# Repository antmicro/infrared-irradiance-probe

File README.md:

# Infrared Irradiance Probe

Copyright (c) 2022-2023 [Antmicro](https://www.antmicro.com)

## Overview

This project contains open hardware design files for a simple detector of infrared (IR) radiation.
It features two photodiodes with peak sensitivity of 900nm and 940nm, and signal-forming circuitry with adjustable gain.
The board can be used for measuring relative intensity of IR radiation and for probing dynamic illumination parameters of infrared LEDs and laser modules.

The design files were prepared in KiCad 6.x.

## Project structure 

The main directory contains KiCad PCB design files, a LICENSE and a README.
The remaining files are stored in the following directories: 

* `lib` - contains the component libraries, 
* `img` - contains graphics for this README,
* `assets` - contains visual assets used for showcasing this board on [Open Hardware Portal](https://openhardware.antmicro.com)

## Key features

* Two photodiodes for measuring IR irradiance (peak sensitivity @ 900nm for diode on top and 940nm for the bottom one)
* BNC connector for oscilloscope measurements
* Regulated sensitivity
* I2C single-channel interface for digital signal probing
* Selectable power source (USB-C / JST / external power supply)

## License

This project is licensed under the [Apache-2.0](LICENSE) license.

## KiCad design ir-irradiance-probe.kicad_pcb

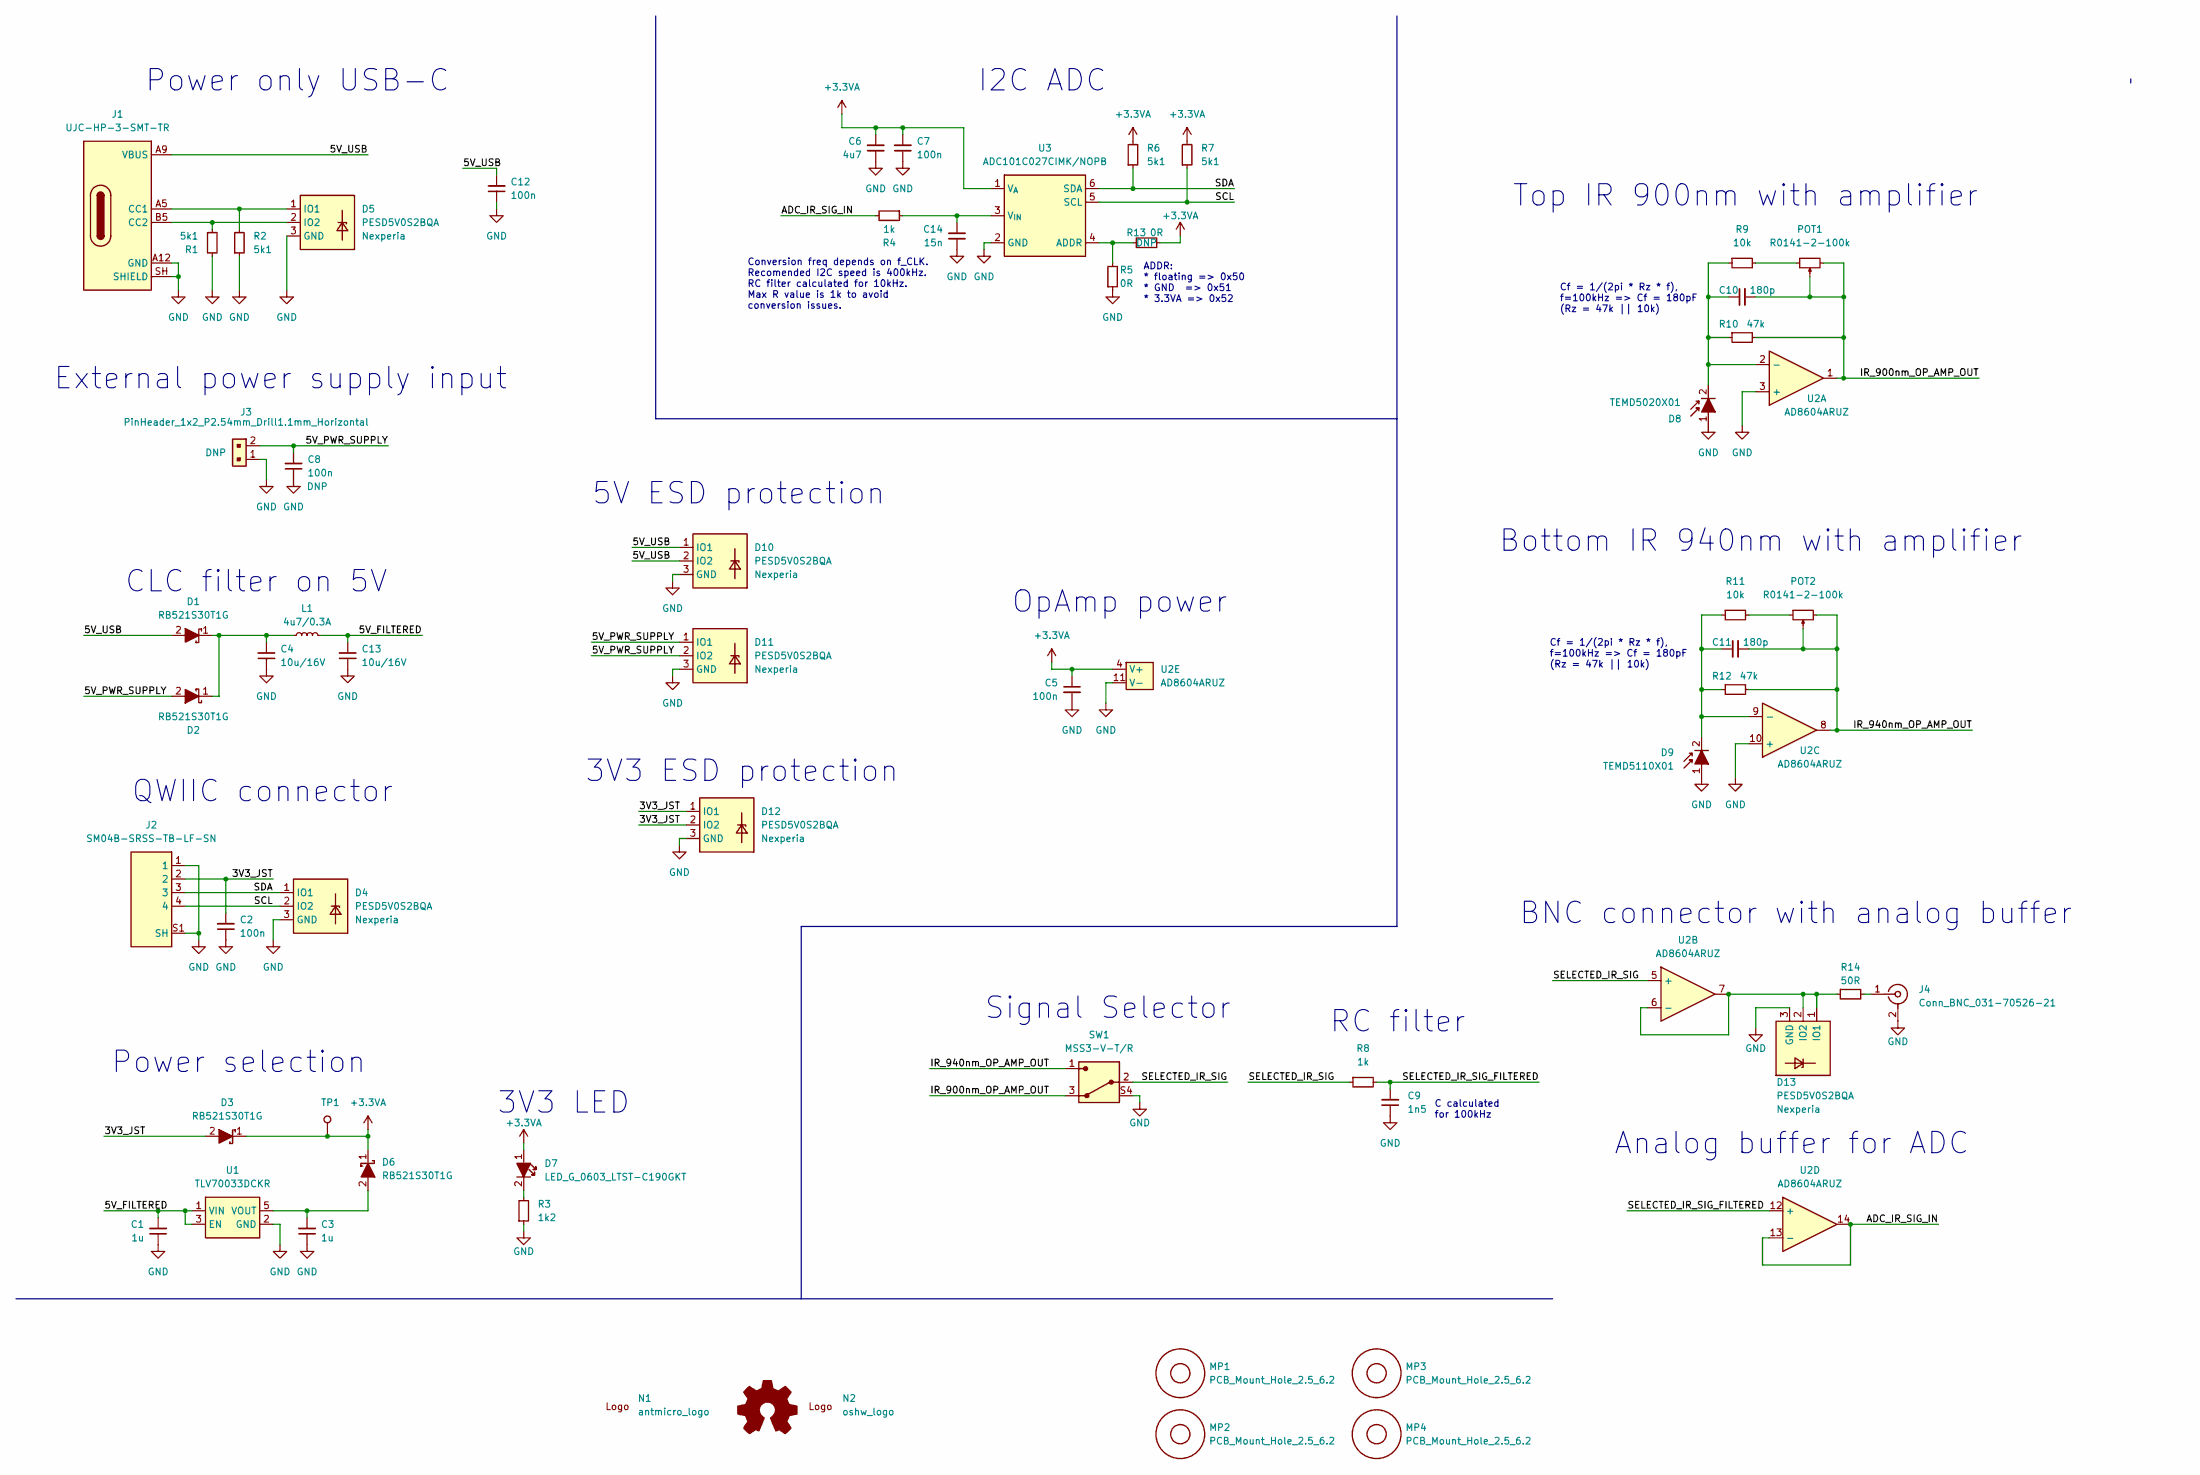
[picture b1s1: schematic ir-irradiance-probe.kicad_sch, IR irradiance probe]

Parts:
C1, C3: C_1u_0402; C_0402_1005Metric; MPN C1005X6S1A105K050BC
C2, C5, C7, C8, C12: C_100n_0402; C_0402_1005Metric; Voltage 50V; MPN GRM155R61H104KE14D
C4, C13: C_10u_16V_0603; C_0603_1608Metric; MPN GRM188C81C106MA73D
C6: C_4u7_0603; C_0603_1608Metric; MPN C1608X5R1V475M080AC
C9: C_1n5_0402; C_0402_1005Metric; MPN 885012205007
C10, C11: C_180p_0402; C_0402_1005Metric; MPN 04025A181JAT2A
C14: C_15n_0402; C_0402_1005Metric; MPN GRM155R71C153KA01D
D1, D2, D3, D6: RB521S30T1G; SOD-523; MPN RB521S30T1G
D4, D5, D10, D11, D12, D13: PESD5V0S2BQA; TPD2E009DRTR; MPN PESD5V0S2BQA
D7: LED_G_0603_LTST-C190GKT; LED_0603_1608Metric_G; MPN LTST-C190GKT
D8: TEMD5020X01; Photodiode_SMD_4.2x5mm_TEMD; MPN TEMD5020X01
D9: TEMD5110X01; Photodiode_SMD_4.2x5mm_TEMD; MPN TEMD5110X01
J1: USB-C_UJC-HP-3-SMT-TR; MPN UJC-HP-3-SMT-TR
J2: SM04B-SRSS-TB-LF-SN; MPN SM04B-SRSS-TB(LF)(SN)
J3: PinHeader_1x2_P2.54mm_Drill1.1mm_Horizontal; PinHeader_1x02_P2.54mm_Horizontal; MPN 61300211021
J4: Conn_BNC_031-70526-21; MPN 031-70526-21
L1: L_4u7_0.3A_0805; L_0805_2012Metric; MPN MLZ2012M4R7HT000
MP1, MP2, MP3, MP4: PCB_Mount_Hole_2.5_6.2; mounting-hole-2.75mm-M2.5_D6.2mm_PTH
N1: antmicro_logo; antmicro-logo_scaled_20mm
N2: oshw_logo; oshw-logo
POT1, POT2: POT_100k_R0141-2-100k; POT_R0141-2; MPN R0141-2-100k
R1, R2, R6, R7: R_5k1_0402; R_0402_1005Metric; Tolerance 1%; MPN CR0402-FX-5101GLF
R3: R_1k2_0402; R_0402_1005Metric; Tolerance 1%; MPN CR0402-FX-1201GLF
R4, R8: R_1k_0402; R_0402_1005Metric; Tolerance 1%; MPN CR0402-FX-1001GLF
R5, R13: R_0R_0402; R_0402_1005Metric; MPN ERJ2GE0R00X
R9, R11: R_10k_0402; R_0402_1005Metric; Tolerance 1%; MPN CR0402-FX-1002GLF
R10, R12: R_47k_0402; R_0402_1005Metric; Tolerance 1%; MPN CR0402-FX-4702GLF
R14: R_50R_0402; R_0402_1005Metric; Tolerance 1%; MPN CR0402-FX-50R0GLF
SW1: MSS3-V-T_R; Switch_Slide_MSS3; MPN MSS3-V-T/R
TP1: TP_0.75mm_SMD; TP_SMD_0.75mm
U1: TLV70033_SC70; SC-70-5; MPN TLV70033DCKR
U2: AD8604ARUZ; TSSOP-14_4.4x5mm_P0.65mm; MPN AD8604ARUZ
U3: ADC101C027CIMK; SOT-23-6; MPN ADC101C027CIMK/NOPB

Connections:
+3.3VA: C5.1, C6.2, C7.2, D3.1, D6.1, D7.1, R6.2, R7.2, R13.1, TP1.1, U2.4 (V+), U3.1 (V_{A})
/3V3_JST: C2.2, D3.2, D12.1 (IO1), D12.2 (IO2), J2.2
/5V_FILTERED: C1.2, C13.2, L1.2, U1.1 (VIN), U1.3 (EN)
/5V_PWR_SUPPLY: C8.2, D2.2, D11.1 (IO1), D11.2 (IO2), J3.2
/5V_USB: C12.2, D1.2, D10.1 (IO1), D10.2 (IO2), J1.A9 (VBUS), J1.B9 (VBUS)
/ADC_IR_SIG_IN: R4.2, U2.13 (-), U2.14
/IR_900nm_OP_AMP_OUT: C10.2, POT1.2, POT1.3, R10.2, SW1.3, U2.1
/IR_940nm_OP_AMP_OUT: C11.2, POT2.2, POT2.3, R12.2, SW1.1, U2.8
/SCL: D4.2 (IO2), J2.4, R7.1, U3.5 (SCL)
/SDA: D4.1 (IO1), J2.3, R6.1, U3.6 (SDA)
/SELECTED_IR_SIG: R8.1, SW1.2, U2.5 (+)
/SELECTED_IR_SIG_FILTERED: C9.2, R8.2, U2.12 (+)
GND: C1.1, C2.1, C3.1, C4.1, C5.2, C6.1, C7.1, C8.1, C9.1, C12.1, C13.1, C14.1, D4.3 (GND), D5.3 (GND), D8.1, D9.1, D10.3 (GND), D11.3 (GND), D12.3 (GND), D13.3 (GND), J1.A12 (GND), J1.B12 (GND), J1.SH (SHIELD), J2.1, J2.S1 (SH), J2.S2 (SH), J3.1, J4.2, R1.2, R2.1, R3.1, R5.1, SW1.S1 (SH), SW1.S2 (SH), SW1.S3 (SH), SW1.S4 (SH), U1.2 (GND), U2.3 (+), U2.10 (+), U2.11 (V-), U3.2 (GND)
unnamed: C3.2, D6.2, U1.5 (VOUT)
unnamed: C4.2, D1.1, D2.1, L1.1
unnamed: C10.1, D8.2, R9.1, R10.1, U2.2 (-)
unnamed: C11.1, D9.2, R11.1, R12.1, U2.9 (-)
unnamed: C14.2, R4.1, U3.3 (V_{IN})
unnamed: D5.1 (IO1), J1.A5 (CC1), R2.2
unnamed: D5.2 (IO2), J1.B5 (CC2), R1.1
unnamed: D7.2, R3.2
unnamed: D13.1 (IO1), D13.2 (IO2), R14.1, U2.6 (-), U2.7
unnamed: J4.1, R14.2
unnamed: POT1.1, R9.2
unnamed: POT2.1, R11.2
unnamed: R5.2, R13.2, U3.4 (ADDR)

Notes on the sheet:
Signal Selector
CLC filter on 5V
BNC connector with analog buffer
Top IR 900nm with amplifier
ADDR: * floating => 0x50 * GND => 0x51 * 3.3VA => 0x52
RC filter
3V3 ESD protection
Cf = 1/(2pi * Rz * f), f=100kHz => Cf = 180pF (Rz = 47k || 10k)
I2C ADC
Conversion freq depends on f_CLK. Recomended I2C speed is 400kHz. RC filter calculated for 10kHz. Max R value is 1k to avoid conversion issues.
Power only USB-C
Analog buffer for ADC
Power selection
External power supply input
OpAmp power
QWIIC connector
Bottom IR 940nm with amplifier
3V3 LED
5V ESD protection
C calculated for 100kHz

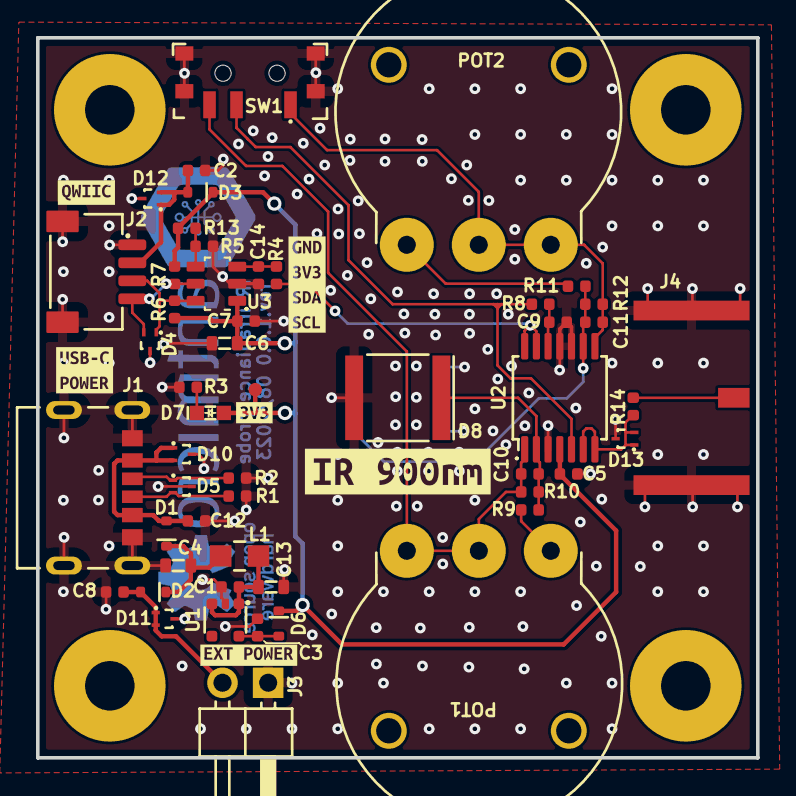
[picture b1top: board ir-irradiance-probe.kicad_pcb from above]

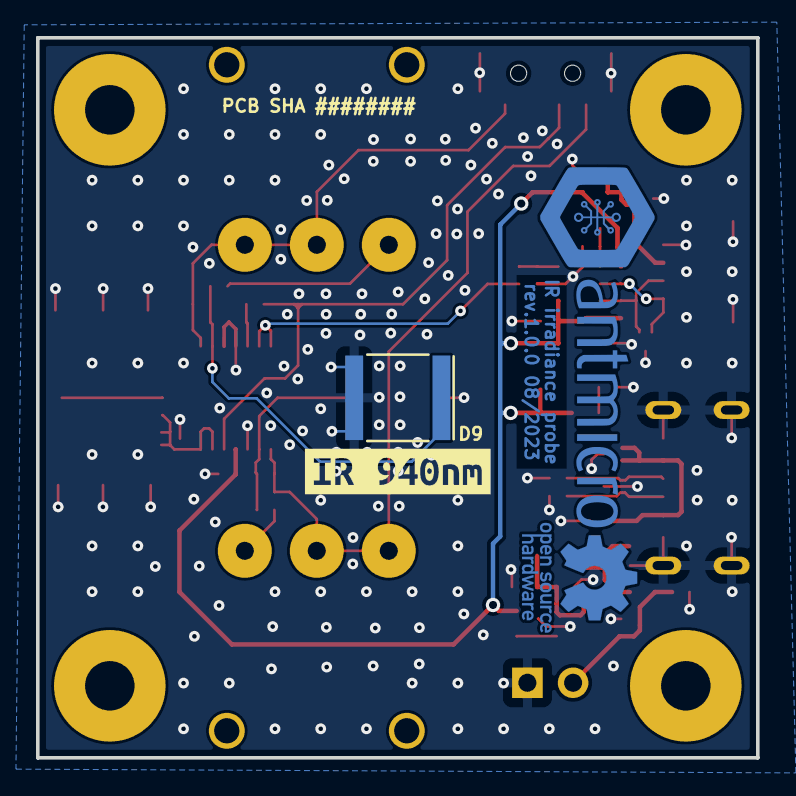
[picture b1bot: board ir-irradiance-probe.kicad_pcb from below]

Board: 2 copper layers, 40.0 x 40.0 mm, 66 parts (4 on the bottom side), 26 nets.

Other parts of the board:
kibuzzard-64C24E37: G***; kibuzzard-64C24E37
kibuzzard-64C24E46: G***; kibuzzard-64C24E46
kibuzzard-64DA12EE: G***; kibuzzard-64DA12EE
kibuzzard-64DA14BC: G***; kibuzzard-64DA14BC
kibuzzard-64DA143B: G***; kibuzzard-64DA143B
kibuzzard-64DA1325: G***; kibuzzard-64DA1325
kibuzzard-64E321C3: G***; kibuzzard-64E321C3

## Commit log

2023-07-27 [#47284] Create empty kicad project
2023-07-27 [#47284] Add README file
2023-07-27 [#47284] Add layout for visual reference and power connectors on sch
2023-07-27 [#47284] Add ADC and mounting holes on sch
2023-07-28 [#47284] Update block diagram
2023-07-28 [#47284] Add analog section to sch
2023-07-28 [#47284] Add power section
2023-08-03 [#47284] Update RC filter with C value
2023-08-03 [#47284] Connect IR signals to the switch
2023-08-03 [#47284] Complete circuit for I2C ADC
2023-08-03 [#47284] Add TVS diodes on USB-C and QWIIC connectors
2023-08-03 [#47284] Add 100n capacitor on OpAmp power pin
2023-08-03 [#47284] Add proper values for CLC filter
2023-08-03 [#47284] Update C values in OpAmp circuit and annotate schematic
2023-08-03 [#47284] Update schematic with symbols from antmicro symlib
2023-08-03 [#47284] Add LED indicator on 3V3 power line
2023-08-07 [#47284] Update potentiometers for amplifiers
2023-08-07 [#47284] Cleaned schematic
2023-08-07 [#47284] Migrated project back to KiCad v6
2023-08-07 [#47284] Minor fixes in schematic
2023-08-07 [#47284] Prepare preliminary components layout
2023-08-09 [#47284] Update potentiometer after standardisation
2023-08-09 [#47284] Create local components library
2023-08-09 [#47284] Change potentiometers on schematic
2023-08-09 [#47284] Rework PCB layout to fit 4x4cm board
2023-08-09 [#47284] Change pin header to horizontal
2023-08-10 [#47284] Update local lib
2023-08-10 [#47284] Mark J3 PinHeader as DNP
2023-08-10 [#47284] Change bottom photodiode from TEMD5020X01 to TEMD5110X01
2023-08-10 [#47284] Unified text size on schematic
2023-08-10 [#47284] Update project info and add logo
2023-08-10 [#47284] Update USB circuit
2023-08-10 [#47284] Update PinHeader circuit
2023-08-10 [#47284] Update JST circuit
2023-08-10 [#47284] Fixed 3V3 LED circuit
2023-08-10 [#47284] Updated RC filter on ADC input line
2023-08-10 [#47284] Updated CLC filter on 5V line
2023-08-10 [#47284] Add ESD protection on BNC connector
2023-08-10 [#47284] Annotated components and reorganised schematic
2023-08-10 [#47284] Updated PCB layout
2023-08-10 [#47284] Run kmake loclib
2023-08-14 [#47284] Standardized the rest of the components
2023-08-14 [47284] Set stackup and constraints
2023-08-14 [47284] Add preliminary routing
2023-08-14 [47284] Clear DRC errors and warnings
2023-08-14 [47284] Add pcb sha string
2023-08-14 [47284] Add connectors labels
2023-08-18 [#47284] Fix antmicro and ohw logos positioning
2023-08-18 [#47284] Fix routing
2023-08-18 [#47284] Changed stackup to EC_2_Layers_Standard
2023-08-18 [#47284] Add copper plane on bottom layer
2023-08-18 [#47284] Add vias on 2.54mm grid
2023-08-18 [#47284] Fix potentiometer labels position
2023-08-21 [#47284] Add 50R resistor on BNC connector
2023-08-21 [#47284] Remove DNP attribute from C10 and C11
2023-08-21 [#47284] Add label and TestPoint near 3V3 LED
2023-11-08 [#47284] Update footprint for SW1, add OHP assets

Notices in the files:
parts and their libraries:
License: Apache-2.0
